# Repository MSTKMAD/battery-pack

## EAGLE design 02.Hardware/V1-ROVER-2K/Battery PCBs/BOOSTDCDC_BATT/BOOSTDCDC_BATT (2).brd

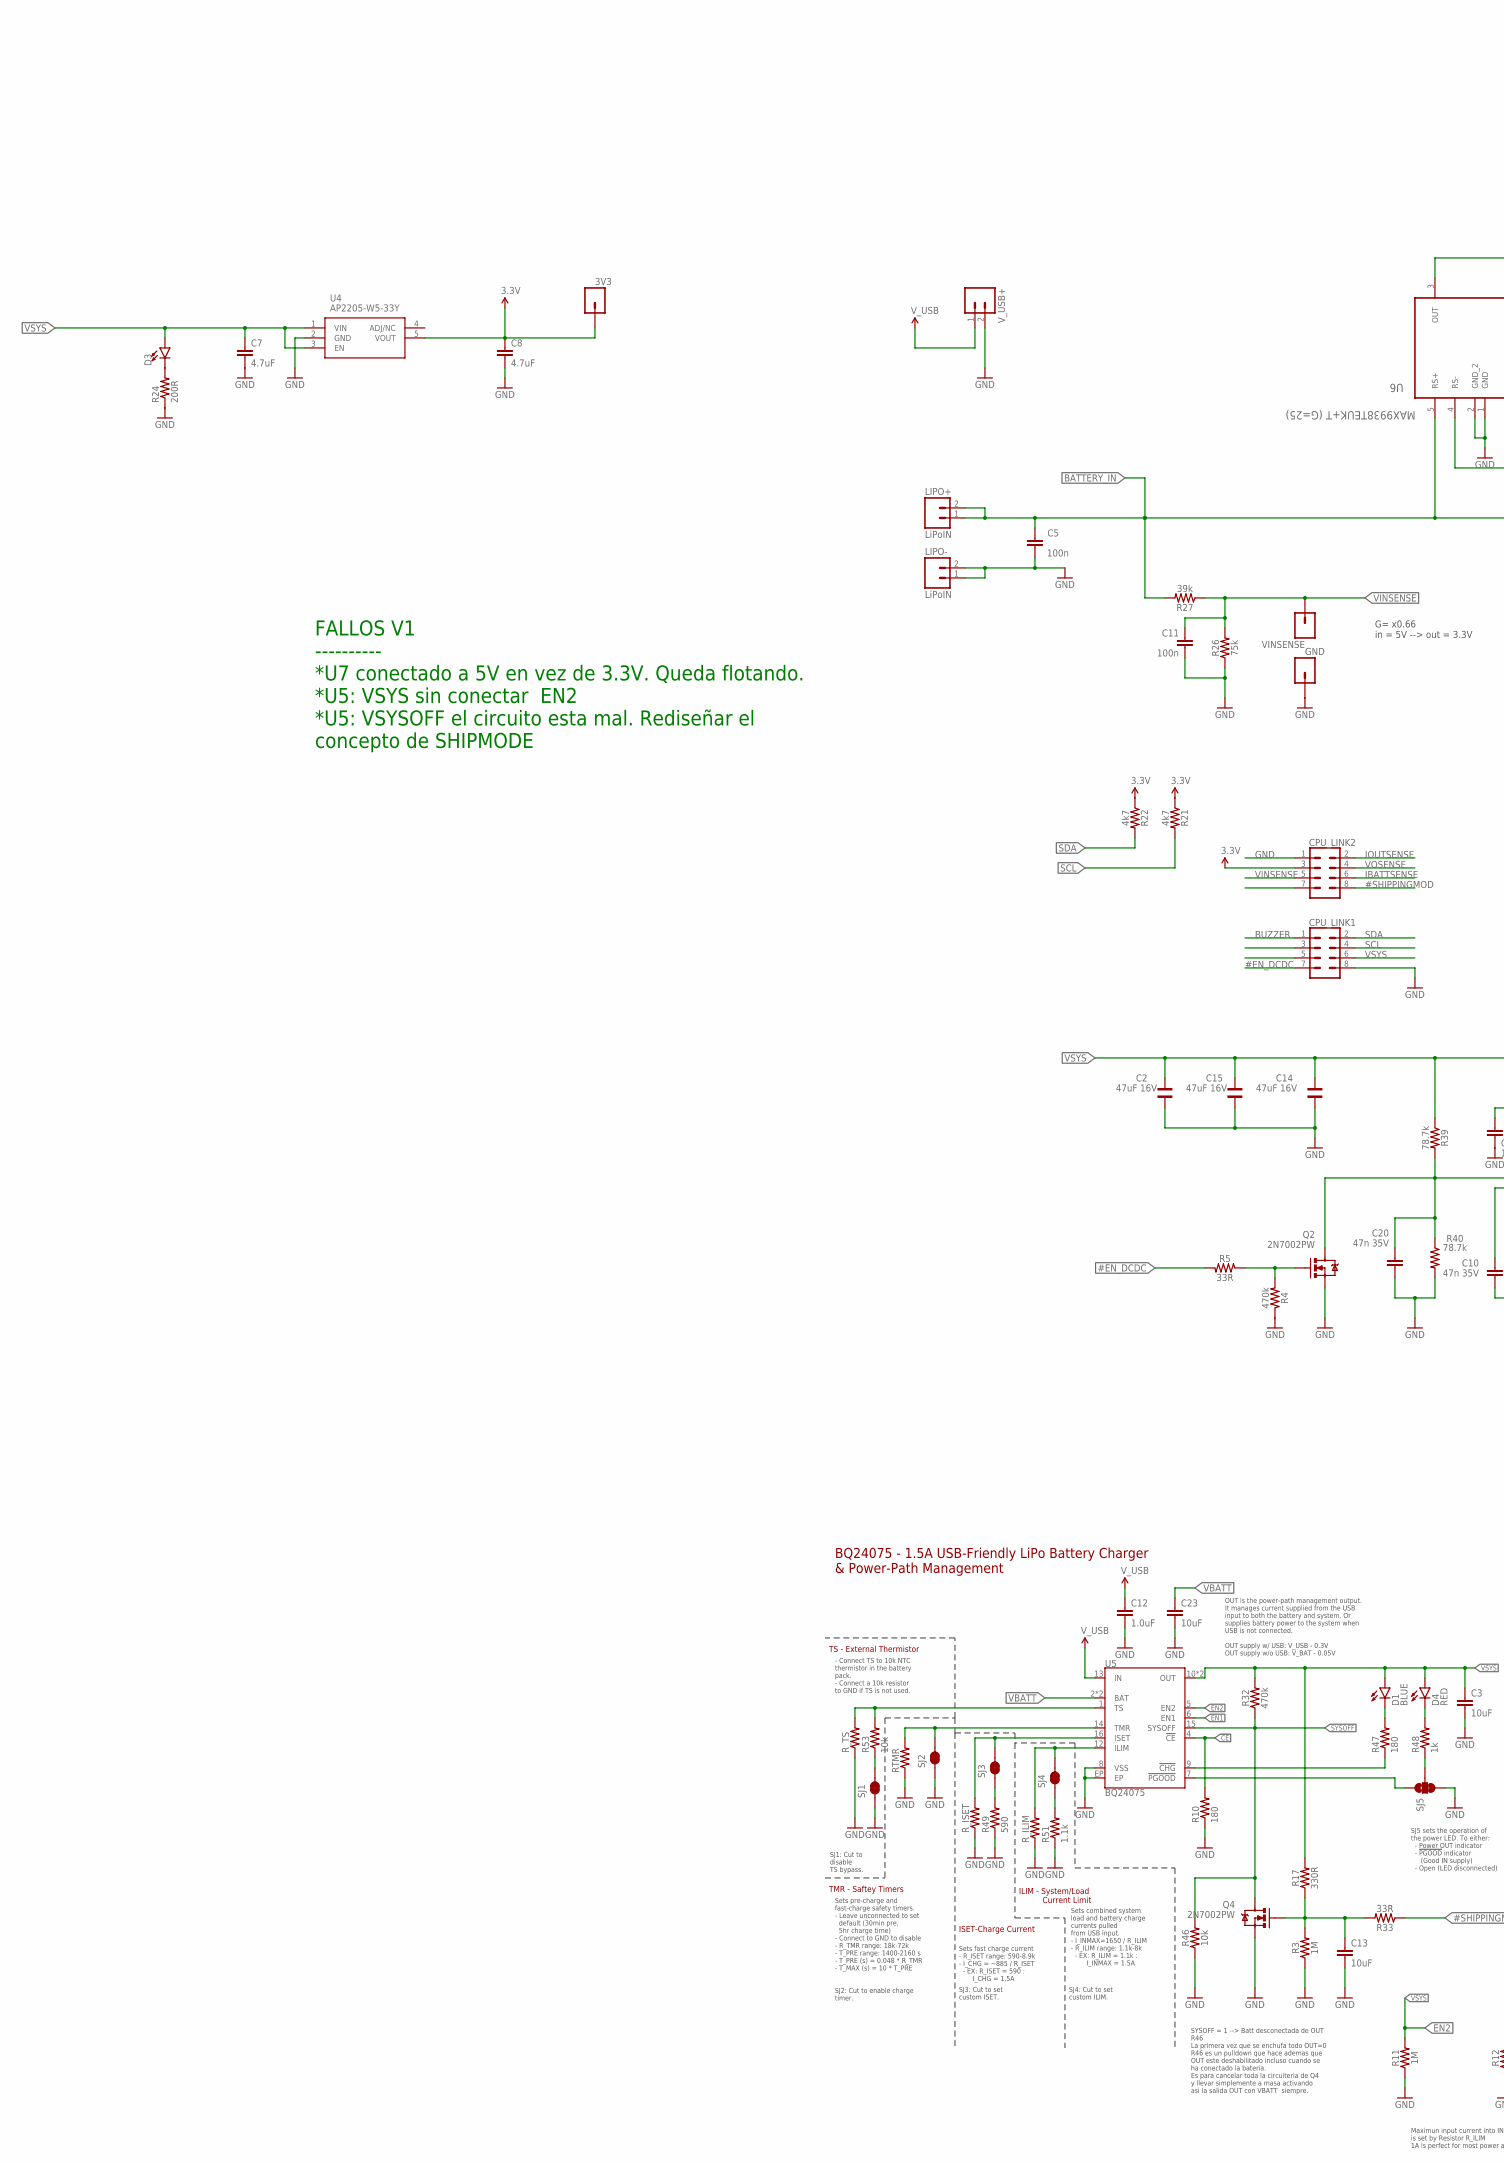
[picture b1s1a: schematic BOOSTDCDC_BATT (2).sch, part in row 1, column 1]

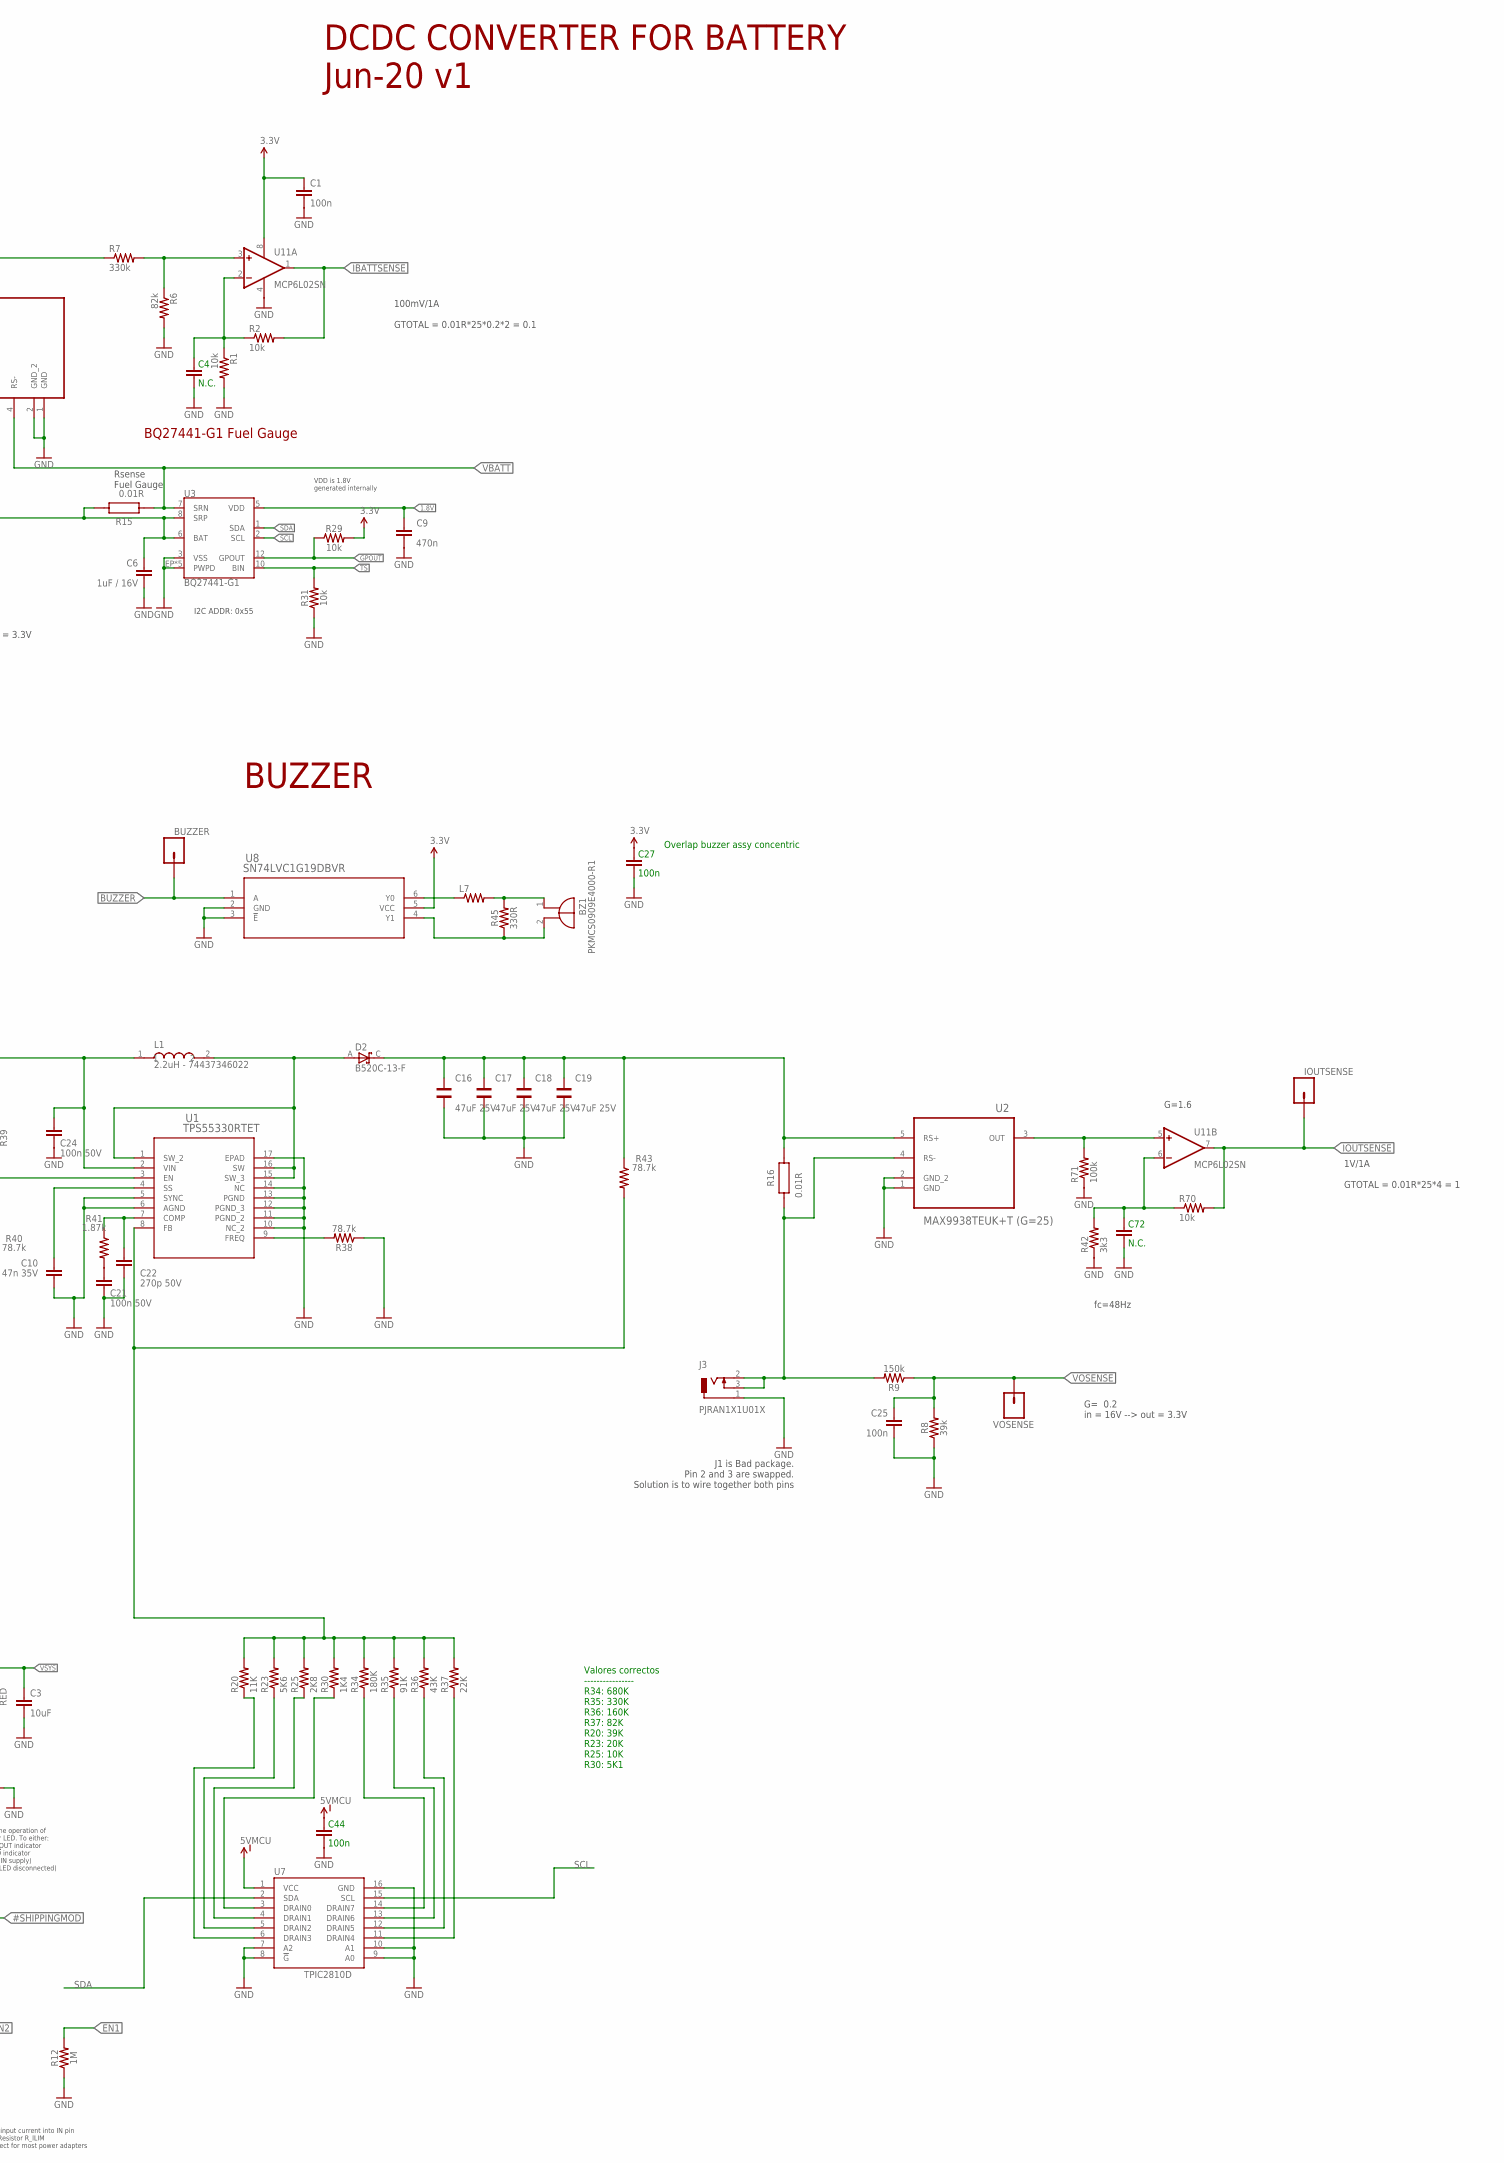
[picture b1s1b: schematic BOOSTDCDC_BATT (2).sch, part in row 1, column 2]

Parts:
3V3: M01PTH_2MM; 1X01_2MM
BUZZER: M01PTH_2MM; 1X01_2MM
BZ1: PKMCS0909E4000-R1; PKMCS0909
C1, C27, C44: 100n; 0805
C2, C14, C15: 47uF 16V; WCAP-CSGP_1210
C3, C13, C23: 10uF; 0805-CAP
C4, C72: N.C.; 0805
C5, C11, C25: 100n; 0805@1
C6: 1uF / 16V; 0805@1
C7, C8: 4.7uF; 0805
C9: 470n; 0805@1
C10, C20: 47n 35V; 0805@1
C12: 1.0uF; 1206-CAP
C16, C17, C18, C19: 47uF 25V; WCAP-CSGP_1210
C21, C24: 100n 50V; 0805@1
C22: 270p 50V; 0805@1
CPU_LINK1, CPU_LINK2: CONN_04X2; 2X4
D1: BLUE; LED-0603
D2: B520C-13-F; DIOM7959X250N
D3: LED3MM; LED_3MM
D4: RED; LED-0603
GND: M01PTH_2MM; 1X01_2MM
IOUTSENSE: M01PTH_2MM; 1X01_2MM
J3: PJRAN1X1U01X
L1: 2.2uH - 74437346022; INDM7366X500
L7: MMZ2012Y202BT000; 0805
LIPO+: LiPoIN; 1X02
LIPO-: LiPoIN; 1X02
Q2, Q4: 2N7002PW; SOT323
R1, R2, R29, R31, R46, R53, R70: 10k; 0805
R3, R11, R12: 1M; 0805
R4, R32: 470k; 0805
R5, R33: 33R; 0805
R6: 82k; 0805
R7: 330k; 0805
R8, R27: 39k; 0805
R9: 150k; 0805
R10, R47: 180; 0805
R15, R16: 0.01R; WRIS-KWKH_0612
R17, R45: 330R; 0805
R20: 11K; 0805
R21, R22: 4k7; 0805
R23: 5K6; 0805
R24: 200R; 0805
R25: 2K8; 0805
R26: 75k; 0805
R30: 1K4; 0805
R34: 180K; 0805
R35: 91K; 0805
R36: 43K; 0805
R37: 22K; 0805
R38, R39, R40, R43: 78.7k; 0805
R41: 1.87k; 0805
R42: 3k3; 0805
R48: 1k; 0805
R49: 590; 0805
R51: 1.1k; 0805
R71: 100k; 0805
RTMR: RESISTOR0805-RES; 0805
R_ILIM: RESISTOR0805-RES; 0805
R_ISET: RESISTOR0805-RES; 0805
R_TS: RESISTOR0805-RES; 0805
SJ1, SJ2, SJ3, SJ4: JUMPER-PAD-2-NC_BY_TRACE; PAD-JUMPER-2-NC_BY_TRACE_YES_SILK
SJ5: JUMPER-PAD-3-2OF3_NC_BY_TRACE_SMALL; PAD-JUMPER-3-2OF3_NC_BY_TRACE_YES_SILK_FULL_BOX
U1: TPS55330RTET; RTE16_1P66X1P66_TEX
U2, U6: MAX9938TEUK+T (G=25); SOT95P280X145-5N
U3: BQ27441-G1; PDSO-N12
U4: AP2205-W5-33Y; SOT95P282X145-5N
U5: BQ24075; PVQFN-N16
U7: TPIC2810D; SO16
U8: SN74LVC1G19DBVR; DBV6
U11: MCP6L02SN; SO08
VINSENSE: M01PTH_2MM; 1X01_2MM
VOSENSE: M01PTH_2MM; 1X01_2MM
V_USB+: M02PTH; 1X02

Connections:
1.8V: C9.1, U3.5 (VDD)
3.3V: 3V3.1, C1.1, C8.1, C27.2, CPU_LINK2.3, R21.1, R22.1, R29.2, U4.5 (VOUT), U8.5 (VCC), U11.8 (V+)
!CE!: R10.2, U5.4 (!CE!)
!CHG!: R47.1, U5.9 (!CHG!)
!PGOOD!: SJ5.1, U5.7 (!PGOOD!)
#EN_DCDC: CPU_LINK1.7, R5.2
#SHIPPINGMOD: CPU_LINK2.8, R33.1
BATTERY_IN: C5.1, C6.1, LIPO+.1, LIPO+.2, R15.2, R27.2, U3.6 (BAT), U3.8 (SRP), U6.5 (RS+)
BUZZER: BUZZER.1, CPU_LINK1.1, U8.1 (A)
EN1: R12.2, U5.6 (EN1)
EN2: R11.2, U5.5 (EN2)
GND: C1.2, C2.1, C3.2, C4.1, C5.2, C6.2, C7.2, C8.2, C9.2, C10.2, C11.2, C12.2, C13.2, C14.1, C15.1, C16.1, C17.1, C18.1, C19.1, C20.2, C21.1, C22.1, C23.2, C24.1, C25.2, C27.1, C44.1, C72.1, CPU_LINK1.8, CPU_LINK2.1, GND.1, J3.1, LIPO-.1, LIPO-.2, Q2.2 (S), Q4.2 (S), R1.2, R3.1, R4.1, R6.2, R8.1, R10.1, R11.1, R12.1, R24.1, R26.1, R31.1, R38.1, R40.2, R42.1, R46.1, R49.1, R51.1, R71.1, RTMR.1, R_ILIM.1, R_ISET.1, R_TS.1, SJ1.1, SJ2.1, SJ5.3, U1.5 (SYNC), U1.6 (AGND), U1.10 (NC_2), U1.11 (PGND_2), U1.12 (PGND_3), U1.13 (PGND), U1.14 (NC), U1.17 (EPAD), U2.1 (GND), U2.2 (GND_2), U3.3 (VSS), U3.EP (PWPD), U3.EP1 (PWPD), U3.EP2 (PWPD), U3.EP3 (PWPD), U3.EP4 (PWPD), U4.2 (GND), U5.8 (VSS), U5.EP, U6.1 (GND), U6.2 (GND_2), U7.7 (A2), U7.8 (!G), U7.9 (A0), U7.10 (A1), U7.16 (GND), U8.2 (GND), U8.3 (!E), U11.4 (V-), V_USB+.2
GPOUT: R29.1, U3.12 (GPOUT)
IBATTSENSE: CPU_LINK2.6, R2.2, U11.1 (OUT)
ILIM: R_ILIM.2, SJ4.2, U5.12 (ILIM)
IOUTSENSE: CPU_LINK2.2, IOUTSENSE.1, R70.2, U11.7 (OUT)
ISET: R_ISET.2, SJ3.2, U5.16 (ISET)
unnamed: D4.C, R48.2
unnamed: Q2.1 (G), R4.2, R5.1
unnamed: D1.C, R47.2
unnamed: R53.1, SJ1.2
unnamed: R71.2, U2.3 (OUT), U11.5 (+IN)
unnamed: R51.2, SJ4.1
unnamed: C4.2, R1.1, R2.1, U11.2 (-IN)
unnamed: R6.1, R7.2, U11.3 (+IN)
unnamed: J3.2, J3.3, R9.2, R16.1, U2.4 (RS-)
unnamed: R49.2, SJ3.1
unnamed: R48.1, SJ5.2
unnamed: R20.1, U7.6 (DRAIN3)
unnamed: L7.1, U8.6 (Y0)
unnamed: D3.K (C), R24.2
unnamed: BZ1.1 (+), L7.2, R45.2
unnamed: R23.1, U7.5 (DRAIN2)
unnamed: BZ1.2 (-), R45.1, U8.4 (Y1)
unnamed: C13.1, Q4.1 (G), R3.2, R17.1, R33.2
unnamed: R25.1, U7.4 (DRAIN1)
unnamed: R30.1, U7.3 (DRAIN0)
unnamed: R34.1, U7.14 (DRAIN7)
unnamed: R35.1, U7.13 (DRAIN6)
unnamed: R36.1, U7.12 (DRAIN5)
unnamed: R37.1, U7.11 (DRAIN4)
unnamed: C10.1, U1.4 (SS)
unnamed: D2.A, L1.2, U1.1 (SW_2), U1.15 (SW_3), U1.16 (SW)
unnamed: R38.2, U1.9 (FREQ)
unnamed: C20.1, Q2.3 (D), R39.2, R40.1, U1.3 (EN)
unnamed: C21.2, R41.2
unnamed: C22.2, R41.1, U1.7 (COMP)
unnamed: R20.2, R23.2, R25.2, R30.2, R34.2, R35.2, R36.2, R37.2, R43.2, U1.8 (FB)
unnamed: R7.1, U6.3 (OUT)
unnamed: C72.2, R42.2, R70.1, U11.6 (-IN)
SCL: CPU_LINK1.4, R21.2, U3.2 (SCL), U7.15 (SCL)
SDA: CPU_LINK1.2, R22.2, U3.1 (SDA), U7.2 (SDA)
SYSOFF: Q4.3 (D), R32.1, R46.2, U5.15 (SYSOFF)
TMR: RTMR.2, SJ2.2, U5.14 (TMR)
TS: R31.2, U3.10 (BIN)
TS1: R53.2, R_TS.2, U5.1 (TS)
VBATT: C23.1, R15.1, U3.7 (SRN), U5.2 (BAT), U5.3 (BAT), U6.4 (RS-)
VCC-ISO: C44.2, U7.1 (VCC)
VINSENSE: C11.1, CPU_LINK2.5, R26.2, R27.1, VINSENSE.1
VOSENSE: C25.1, CPU_LINK2.4, R8.2, R9.1, VOSENSE.1
VSOURCE: C16.2, C17.2, C18.2, C19.2, D2.C, R16.2, R43.1, U2.5 (RS+)
VSYS: C2.2, C3.1, C7.1, C14.2, C15.2, C24.2, CPU_LINK1.6, D1.A, D3.A, D4.A, L1.1, R17.2, R32.2, R39.1, U1.2 (VIN), U4.1 (VIN), U4.3 (EN), U5.10 (OUT), U5.11 (OUT)
V_USB: C12.1, U5.13 (IN), V_USB+.1

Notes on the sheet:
1V/1A GTOTAL = 0.01R*25*4 = 1
J1 is Bad package. Pin 2 and 3 are swapped. Solution is to wire together both pins
G= x0.66 in = 5V --> out = 3.3V
fc=48Hz
G=1.6
BQ27441-G1 Fuel Gauge
VDD is 1.8V generated internally
I2C ADDR: 0x55
Rsense Fuel Gauge
DCDC CONVERTER FOR BATTERY Jun-20 v1
Sets fast charge current - R_ISET range: 590-8.9k - I_CHG = ~885 / R_ISET - EX: R_ISET = 590 : I_CHG = 1.5A
Sets combined system load and battery charge currents pulled from USB input. - I_INMAX=1650 / R_ILIM - R_ILIM range: 1.1k-8k - EX: R_ILIM = 1.1k : I_INMAX = 1.5A
BQ24075 - 1.5A USB-Friendly LiPo Battery Charger & Power-Path Management
SJ1: Cut to disable TS bypass.
SJ3: Cut to set custom ISET.
SJ4: Cut to set custom ILIM.
ILIM - System/Load Current Limit
ISET-Charge Current
TMR - Saftey Timers
Sets pre-charge and fast-charge safety timers. - Leave unconnected to set default (30min pre, 5hr charge time) - Connect to GND to disable - R_TMR range: 18k-72k - T_PRE range: 1400-2160 s - T_PRE (s) = 0.048 * R_TMR - T_MAX (s) = 10 * T_PRE
SJ2: Cut to enable charge timer.
TS - External Thermistor
- Connect TS to 10k NTC thermistor in the battery pack. - Connect a 10k resistor to GND if TS is not used.
OUT is the power-path management output. It manages current supplied from the USB input to both the battery and system. Or supplies battery power to the system when USB is not connected. OUT supply w/ USB: V_USB - 0.3V OUT supply w/o USB: V_BAT - 0.05V
SJ5 sets the operation of the power LED. To either: - Power OUT indicator - !PGOOD! indicator (Good IN supply) - Open (LED disconnected)
Overlap buzzer assy concentric
BUZZER
SYSOFF = 1 --> Batt desconectada de OUT R46 La primera vez que se enchufa todo OUT=0 R46 es un pulldown que hace ademas que OUT este deshabilitado incluso cuando se ha conectado la bateria. Es para cancelar toda la circuiteria de Q4 y llevar simplemente a masa activando asi la salida OUT con VBATT 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
G= 0.2 in = 16V --> out = 3.3V
Maximun input current into IN pin is set by Resistor R_ILIM 1A is perfect for most power adapters
100mV/1A GTOTAL = 0.01R*25*0.2*2 = 0.1
FALLOS V1 ---------- *U7 conectado a 5V en vez de 3.3V. Queda flotando. *U5: VSYS sin conectar EN2 *U5: VSYSOFF el circuito esta mal. Rediseñar el concepto de SHIPMODE
Valores correctos ---------------- R34: 680K R35: 330K R36: 160K R37: 82K R20: 39K R23: 20K R25: 10K R30: 5K1

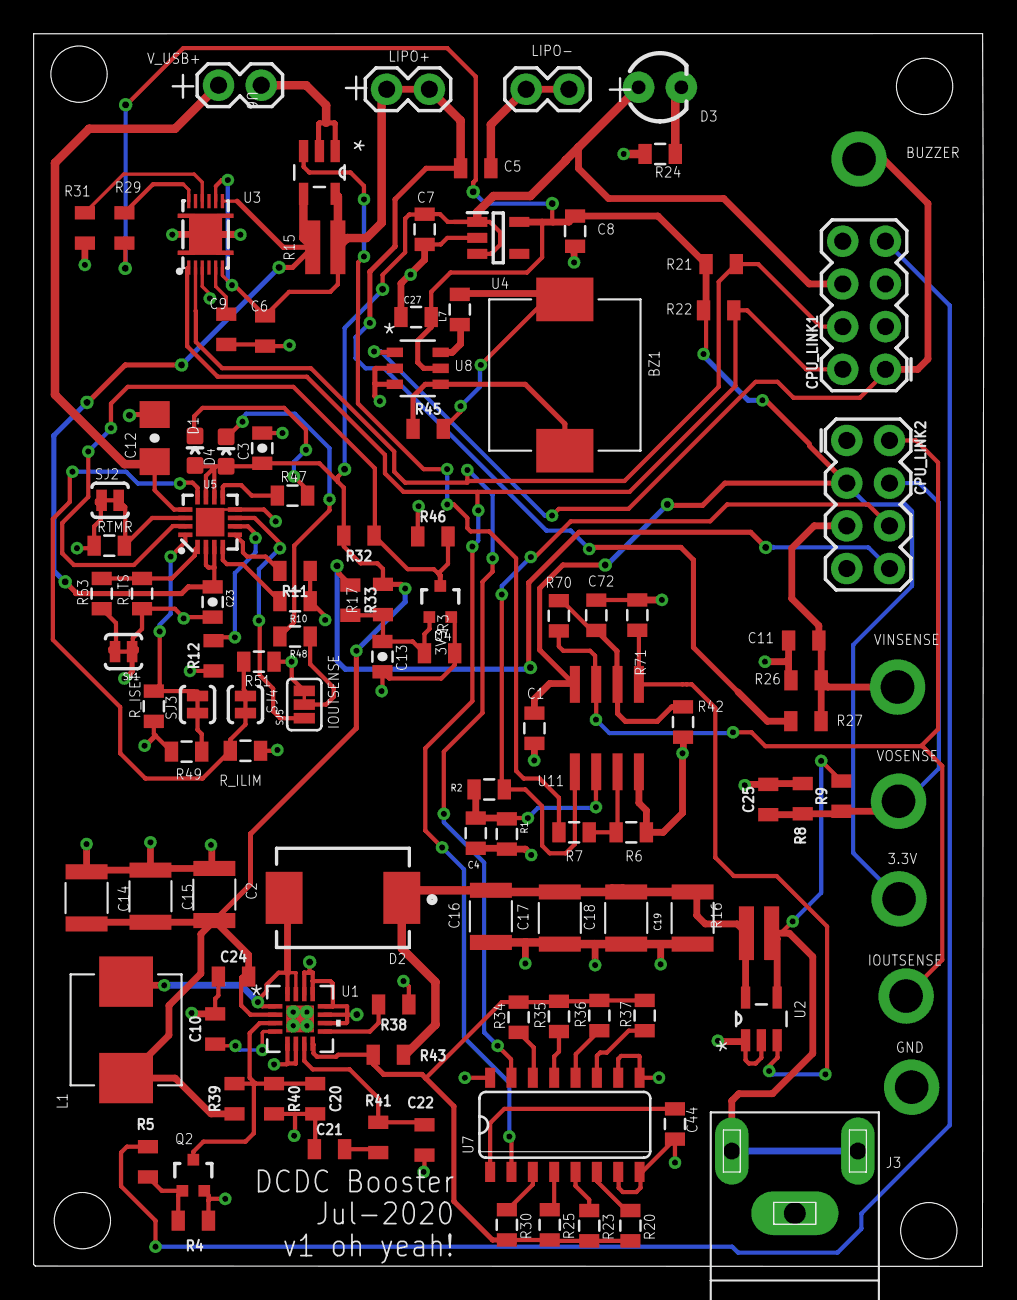
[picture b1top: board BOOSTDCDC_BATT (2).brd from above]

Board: 2 copper layers, 56.5 x 73.3 mm, 114 parts (0 on the bottom side), 63 nets.

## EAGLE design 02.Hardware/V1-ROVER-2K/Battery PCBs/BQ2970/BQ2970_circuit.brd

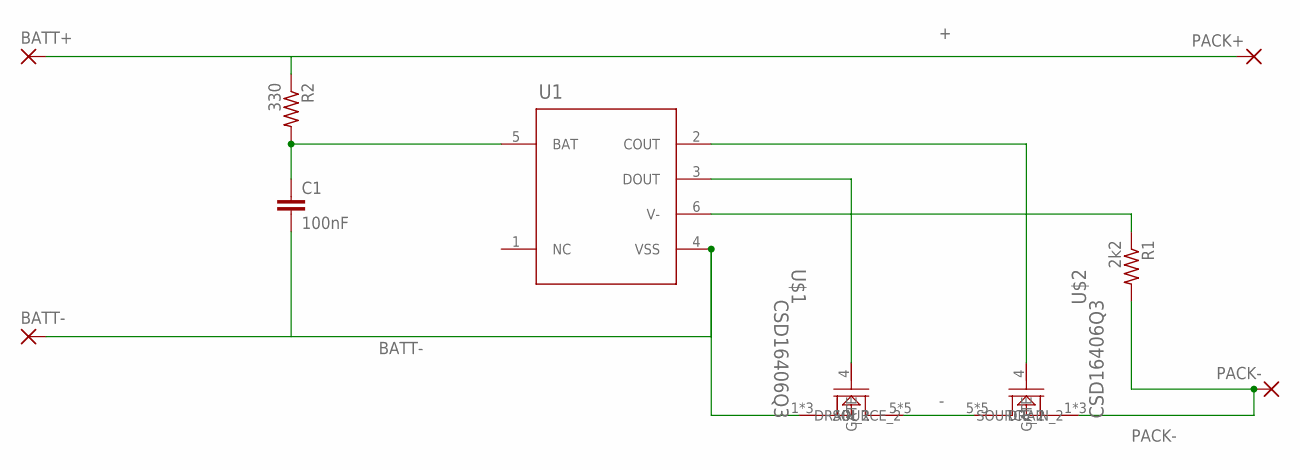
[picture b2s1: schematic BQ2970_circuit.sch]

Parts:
BATT+: SMD5; SMD2,54-5,08
BATT-: SMD5; SMD2,54-5,08
C1: 100nF; C0805
PACK+: SMD5; SMD2,54-5,08
PACK-: SMD5; SMD2,54-5,08
R1: 2k2; R0805
R2: 330; R0805
U1: Value; DSE0006A
U$1, U$2: CSD16406Q3; DQG0008A

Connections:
+: BATT+.1, PACK+.1, R2.1
-: U$1.5 (DRAIN_2), U$1.6 (DRAIN_2), U$1.7 (DRAIN_2), U$1.8 (DRAIN_2), U$1.9 (DRAIN_2), U$2.5 (DRAIN_2), U$2.6 (DRAIN_2), U$2.7 (DRAIN_2), U$2.8 (DRAIN_2), U$2.9 (DRAIN_2)
BATT-: BATT-.1, C1.2, U1.4 (VSS), U$1.1 (SOURCE_2), U$1.2 (SOURCE_2), U$1.3 (SOURCE_2)
unnamed: C1.1, R2.2, U1.5 (BAT)
unnamed: R1.1, U1.6 (V-)
unnamed: U1.2 (COUT), U$2.4 (GATE)
unnamed: U1.3 (DOUT), U$1.4 (GATE)
PACK-: PACK-.1, R1.2, U$2.1 (SOURCE_2), U$2.2 (SOURCE_2), U$2.3 (SOURCE_2)

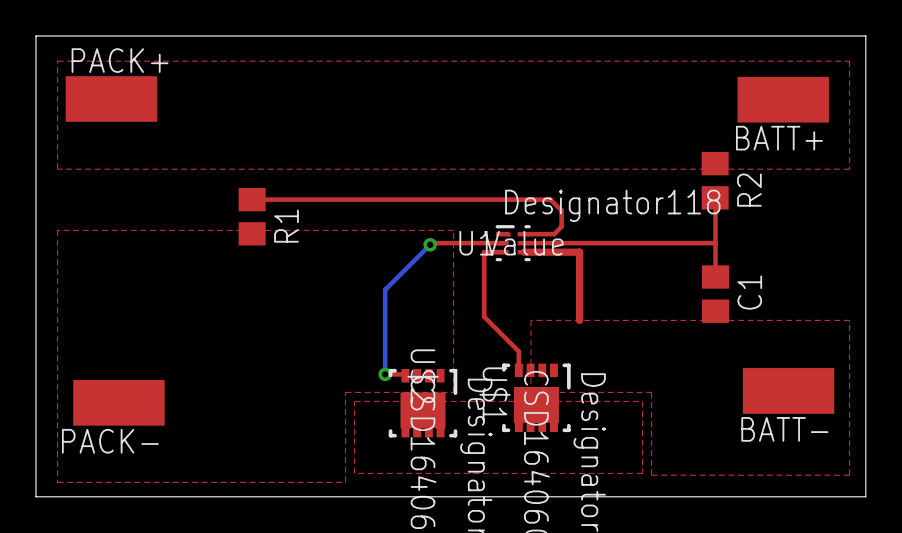
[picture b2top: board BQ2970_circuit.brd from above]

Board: 2 copper layers, 46.1 x 25.6 mm, 10 parts (0 on the bottom side), 8 nets.

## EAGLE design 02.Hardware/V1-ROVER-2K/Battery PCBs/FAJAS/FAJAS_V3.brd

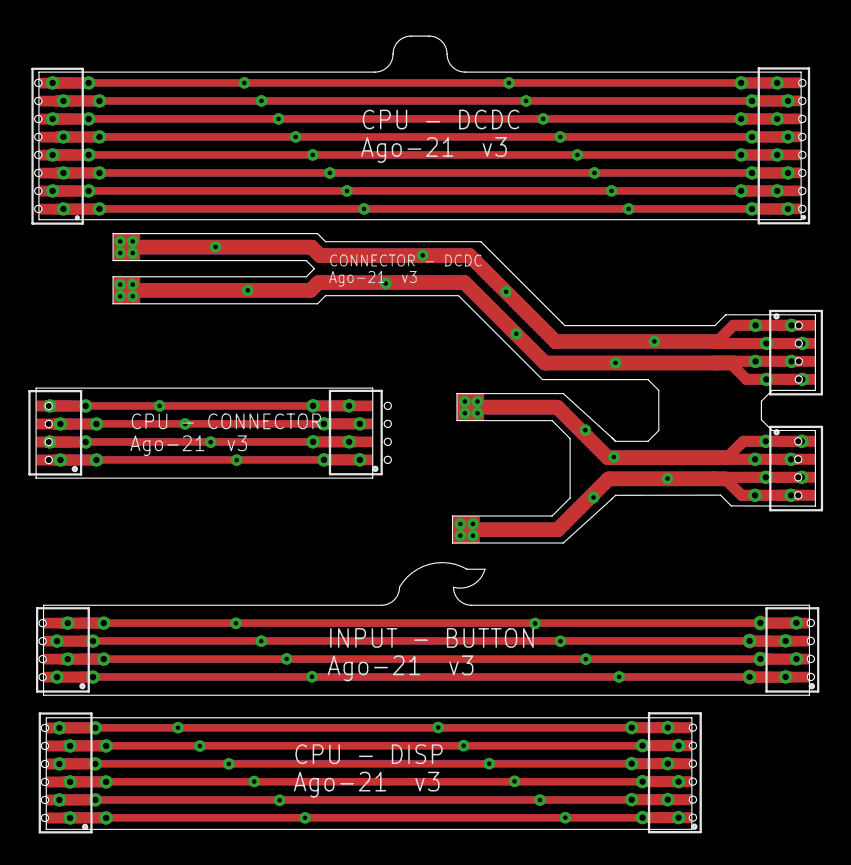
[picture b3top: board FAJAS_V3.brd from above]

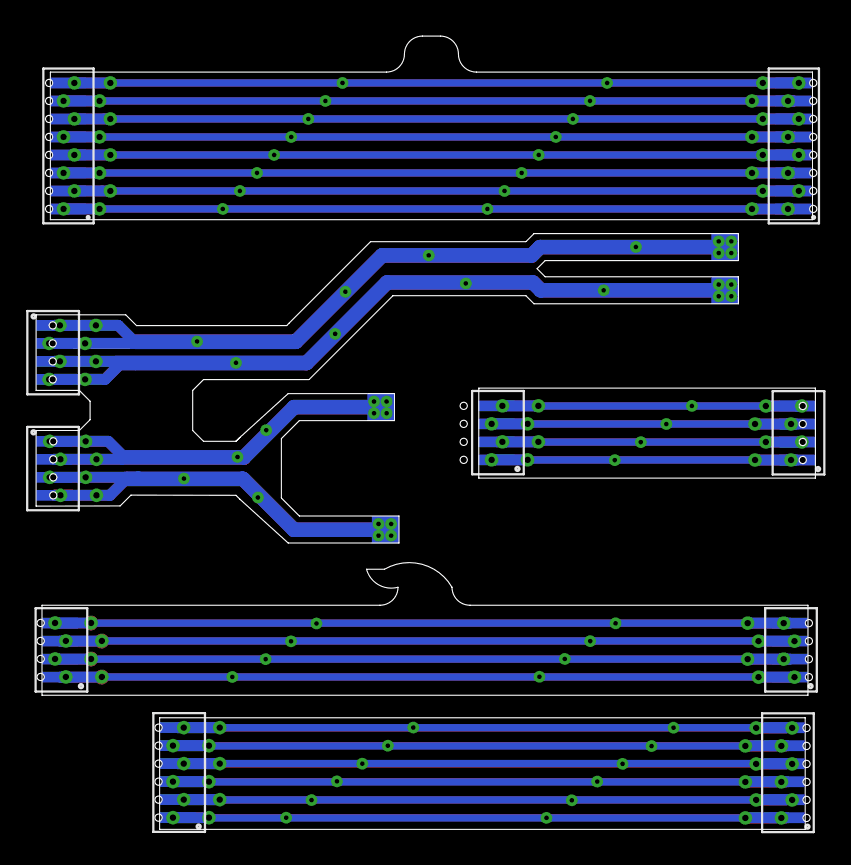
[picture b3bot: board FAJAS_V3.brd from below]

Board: 2 copper layers, 43.3 x 44.1 mm, 28 parts (14 on the bottom side), 26 nets.

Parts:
DISP_CPU_1, DISP_CPU_4: DISP_CPU_1; FLEX6
DISP_CPU_2, DISP_CPU_3: DISP_CPU_2; FLEX6
FLX1, FLX2, FLX3, FLX4, FLX5, FLX6, FLX7, FLX8, FLX9, FLX10, FLX11: FLEX4
GND1, GND2: TESTPAD_TPSQTP15SQ; TESTPAD_TP15SQ
K1, K2: FLEX_DCDC; FLEX8
K3: FLEX_CONN; FLEX4
K4, K5: FLEX8
VO+, VO+1: TESTPAD_TPSQTP15SQ; TESTPAD_TP15SQ
VO-, VO-1: TESTPAD_TPSQTP15SQ; TESTPAD_TP15SQ
VSYS_IP, VSYS_IP1: TESTPAD_TPSQTP15SQ; TESTPAD_TP15SQ

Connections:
BUTTON-INPUT_1: FLX1.1, FLX6.1, FLX8.1, FLX9.1
BUTTON-INPUT_2: FLX1.2, FLX6.2, FLX8.2, FLX9.2
BUTTON-INPUT_3: FLX1.3, FLX6.3, FLX8.3, FLX9.3
BUTTON-INPUT_4: FLX1.4, FLX6.4, FLX8.4, FLX9.4
CPU-CONN_1: FLX3.1, FLX10.1, FLX11.1, K3.1
CPU-CONN_2: FLX3.2, FLX10.2, FLX11.2, K3.2
CPU-CONN_3: FLX3.3, FLX10.3, FLX11.3, K3.3
CPU-CONN_4: FLX3.4, FLX10.4, FLX11.4, K3.4
CPU-DCDC_1: K1.1, K2.1, K4.1, K5.1
CPU-DCDC_2: K1.2, K2.2, K4.2, K5.2
CPU-DCDC_3: K1.3, K2.3, K4.3, K5.3
CPU-DCDC_4: K1.4, K2.4, K4.4, K5.4
CPU-DCDC_5: K1.5, K2.5, K4.5, K5.5
CPU-DCDC_6: K1.6, K2.6, K4.6, K5.6
CPU-DCDC_7: K1.7, K2.7, K4.7, K5.7
CPU-DCDC_8: K1.8, K2.8, K4.8, K5.8
DSP-CPU_1: DISP_CPU_1.1, DISP_CPU_2.1, DISP_CPU_3.1, DISP_CPU_4.1
DSP-CPU_2: DISP_CPU_1.2, DISP_CPU_2.2, DISP_CPU_3.2, DISP_CPU_4.2
DSP-CPU_3: DISP_CPU_1.3, DISP_CPU_2.3, DISP_CPU_3.3, DISP_CPU_4.3
DSP-CPU_4: DISP_CPU_1.4, DISP_CPU_2.4, DISP_CPU_3.4, DISP_CPU_4.4
DSP-CPU_5: DISP_CPU_1.5, DISP_CPU_2.5, DISP_CPU_3.5, DISP_CPU_4.5
DSP-CPU_6: DISP_CPU_1.6, DISP_CPU_2.6, DISP_CPU_3.6, DISP_CPU_4.6
GND: FLX5.1, FLX5.2, FLX7.1, FLX7.2, GND1.TP, GND2.TP
VOUT+: FLX2.1, FLX2.2, FLX4.1, FLX4.2, VO+.TP, VO+1.TP
VOUT-: FLX2.3, FLX2.4, FLX4.3, FLX4.4, VO-.TP, VO-1.TP
VSYS: FLX5.3, FLX5.4, FLX7.3, FLX7.4, VSYS_IP.TP, VSYS_IP1.TP

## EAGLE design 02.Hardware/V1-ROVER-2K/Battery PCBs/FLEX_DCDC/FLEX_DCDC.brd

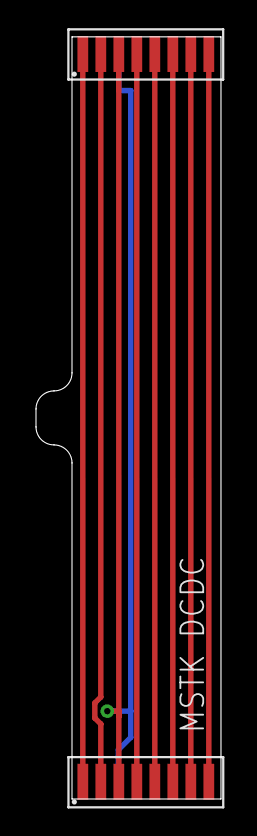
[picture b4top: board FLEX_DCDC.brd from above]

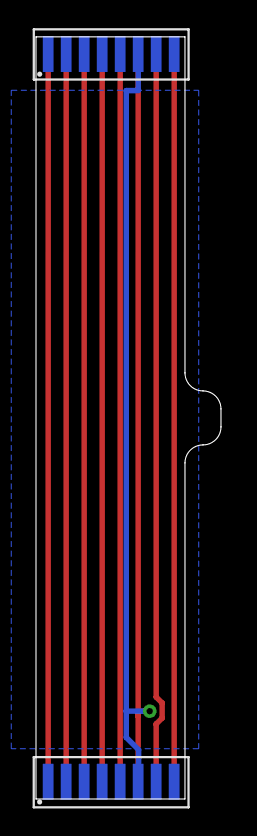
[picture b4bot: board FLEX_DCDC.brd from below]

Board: 2 copper layers, 10.3 x 42.3 mm, 4 parts (2 on the bottom side), 8 nets.

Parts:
K1, K2, K3, K4: FLEX8

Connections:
GND: K1.3, K2.3, K3.6, K4.6
unnamed: K1.1, K2.1
unnamed: K1.2, K2.2
unnamed: K1.4, K2.4
unnamed: K1.5, K2.5
unnamed: K1.6, K2.6
unnamed: K1.7, K2.7
unnamed: K1.8, K2.8

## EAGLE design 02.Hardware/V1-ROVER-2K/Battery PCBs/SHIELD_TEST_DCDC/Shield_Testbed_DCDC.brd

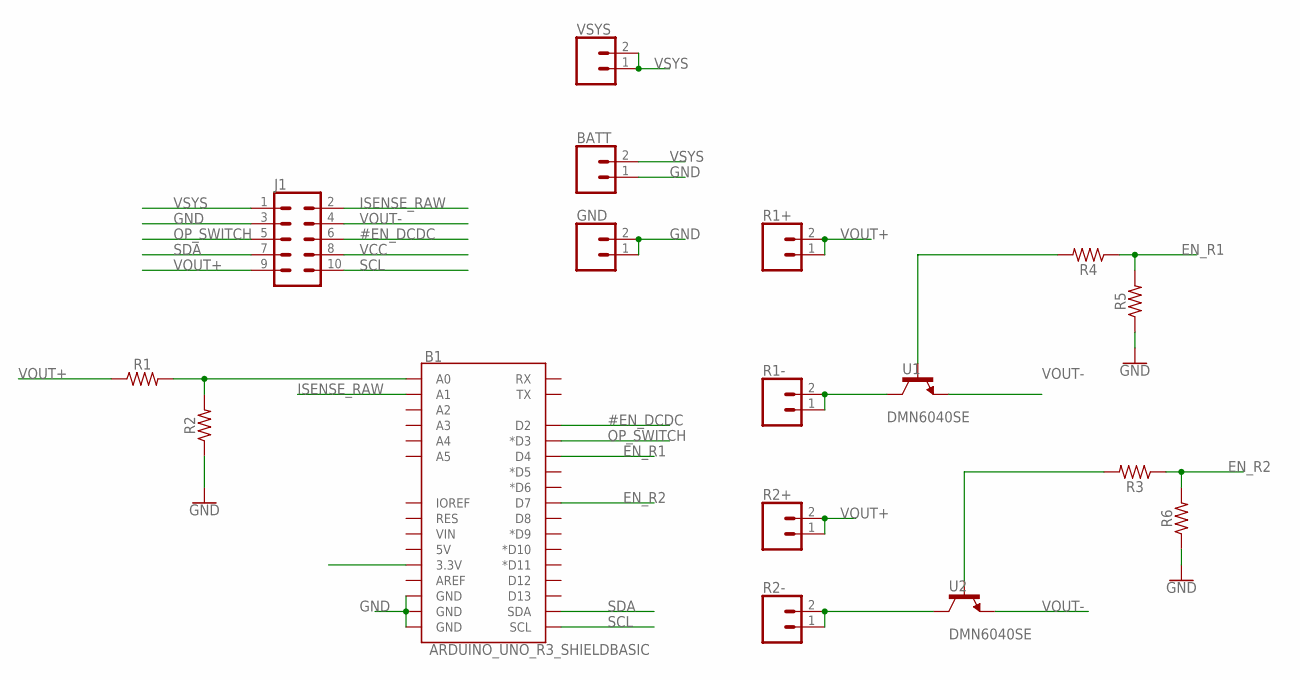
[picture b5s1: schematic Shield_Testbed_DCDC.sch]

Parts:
B1: ARDUINO_UNO_R3_SHIELDBASIC; UNO_R3_SHIELD
BATT: CONN_02; 1X02
GND: CONN_02; 1X02
J1: CONN_05X2PTH; 2X5
R1, R2, R3, R4, R5, R6: 0805
R1+, R1-, R2+, R2-: CONN_02; 1X02
U1, U2: DMN6040SE; SOT-223_3P7X6P7_ONS
VSYS: CONN_02; 1X02

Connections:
#EN_DCDC: B1.D2, J1.6
EN_R1: B1.D4, R4.1, R5.2
EN_R2: B1.D7, R3.1, R6.2
GND: B1.GND@0 (GND), B1.GND@1 (GND), B1.GND@2 (GND), BATT.1, GND.1, GND.2, J1.3, R2.1, R5.1, R6.1
ISENSE_RAW: B1.A1, J1.2
unnamed: B1.A0, R1.2, R2.2
unnamed: R3.2, U2.1 (G)
unnamed: R4.2, U1.1 (G)
OP_SWITCH: B1.D3 (*D3), J1.5
R1-: R1-.1, R1-.2, U1.2 (D), U1.4 (D)
R2-: R2-.1, R2-.2, U2.2 (D), U2.4 (D)
SCL: B1.SCL, J1.10
SDA: B1.SDA, J1.7
VCC: B1.3.3V, J1.8
VOUT+: J1.9, R1.1, R1+.1, R1+.2, R2+.1, R2+.2
VOUT-: J1.4, U1.3 (S), U2.3 (S)
VSYS: BATT.2, J1.1, VSYS.1, VSYS.2

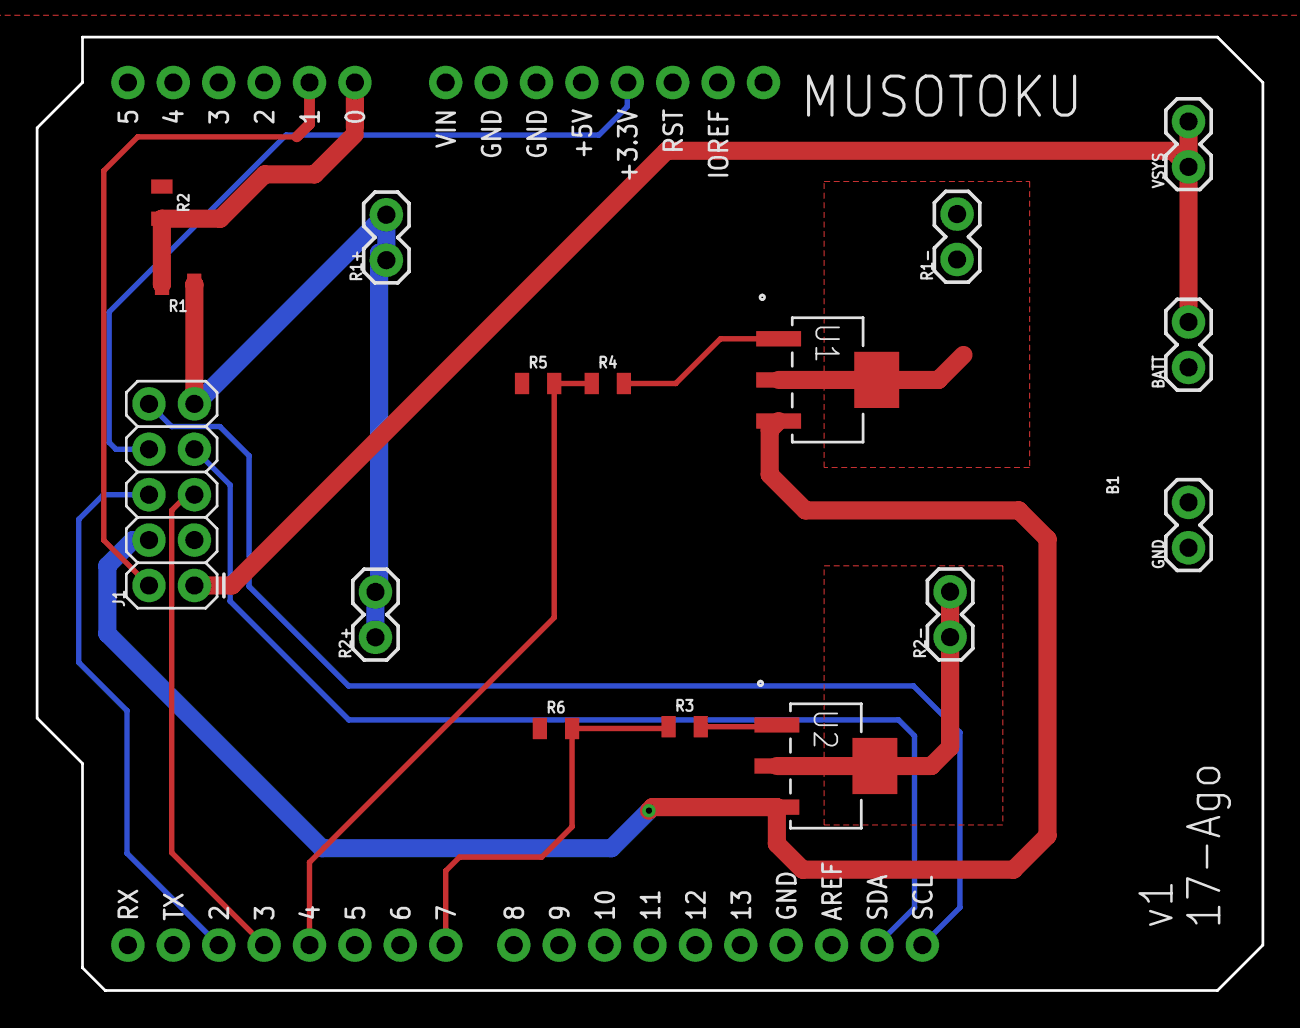
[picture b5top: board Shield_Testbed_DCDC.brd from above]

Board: 2 copper layers, 68.6 x 53.3 mm, 17 parts (0 on the bottom side), 17 nets.

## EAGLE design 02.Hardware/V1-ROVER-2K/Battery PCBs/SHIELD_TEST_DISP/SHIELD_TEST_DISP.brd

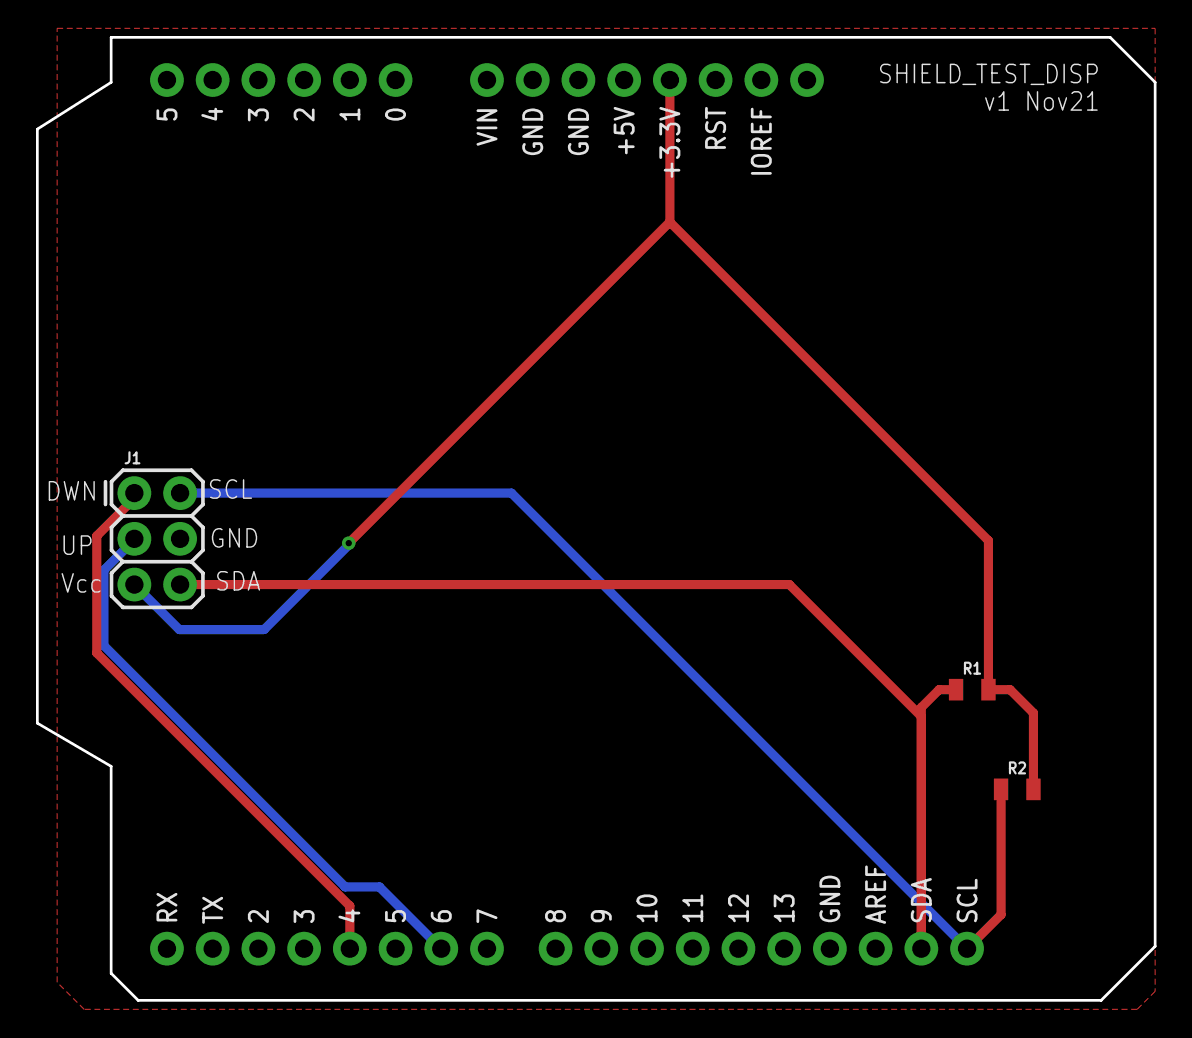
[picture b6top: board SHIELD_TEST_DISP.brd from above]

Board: 2 copper layers, 62.1 x 53.5 mm, 4 parts (0 on the bottom side), 6 nets.

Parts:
B1: ARDUINO_UNO_R3_SHIELDBASIC; UNO_R3_SHIELD
J1: FEMALE 2x3; 2X3
R1, R2: 0805

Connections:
DOWN: B1.D4, J1.1
GND: B1.GND@0, B1.GND@1, B1.GND@2, J1.4
SCL: B1.SCL, J1.2, R2.1
SDA: B1.SDA, J1.6, R1.1
UP: B1.D6, J1.3
VCC: B1.3.3V, J1.5, R1.2, R2.2

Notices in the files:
parts and their libraries:
SparkFun-Passives: Licensing: CC v3.0 Share-Alike You are welcome to use this library for commercial purposes.
SparkFun-LED: Licensing: Creative Commons ShareAlike 4.0 International - https://creativecommons.org/licenses/by-sa/4.0
Wurth_Resistor_WRIS-KWKH: Copyright: Würth Elektronik
